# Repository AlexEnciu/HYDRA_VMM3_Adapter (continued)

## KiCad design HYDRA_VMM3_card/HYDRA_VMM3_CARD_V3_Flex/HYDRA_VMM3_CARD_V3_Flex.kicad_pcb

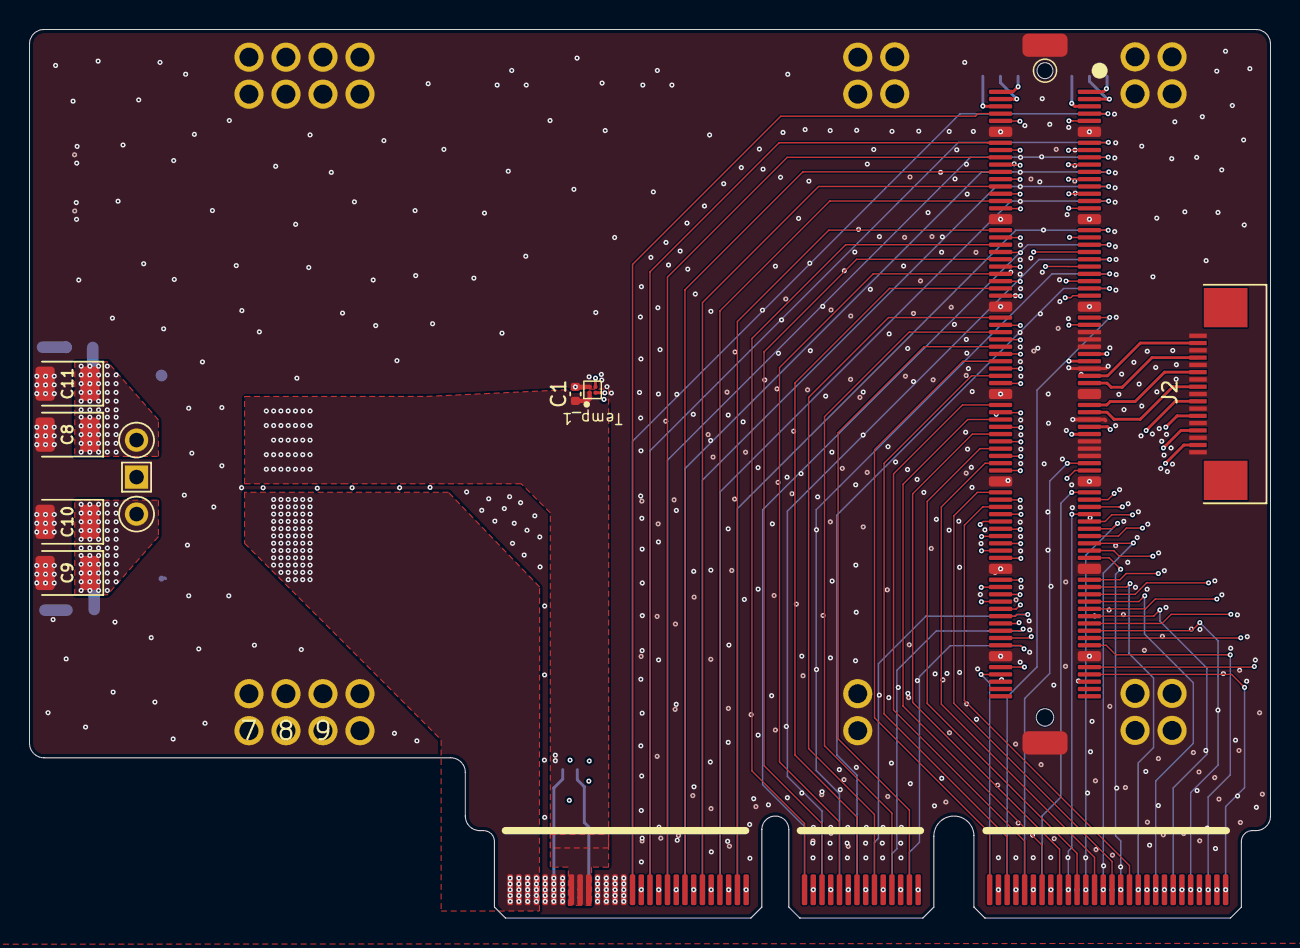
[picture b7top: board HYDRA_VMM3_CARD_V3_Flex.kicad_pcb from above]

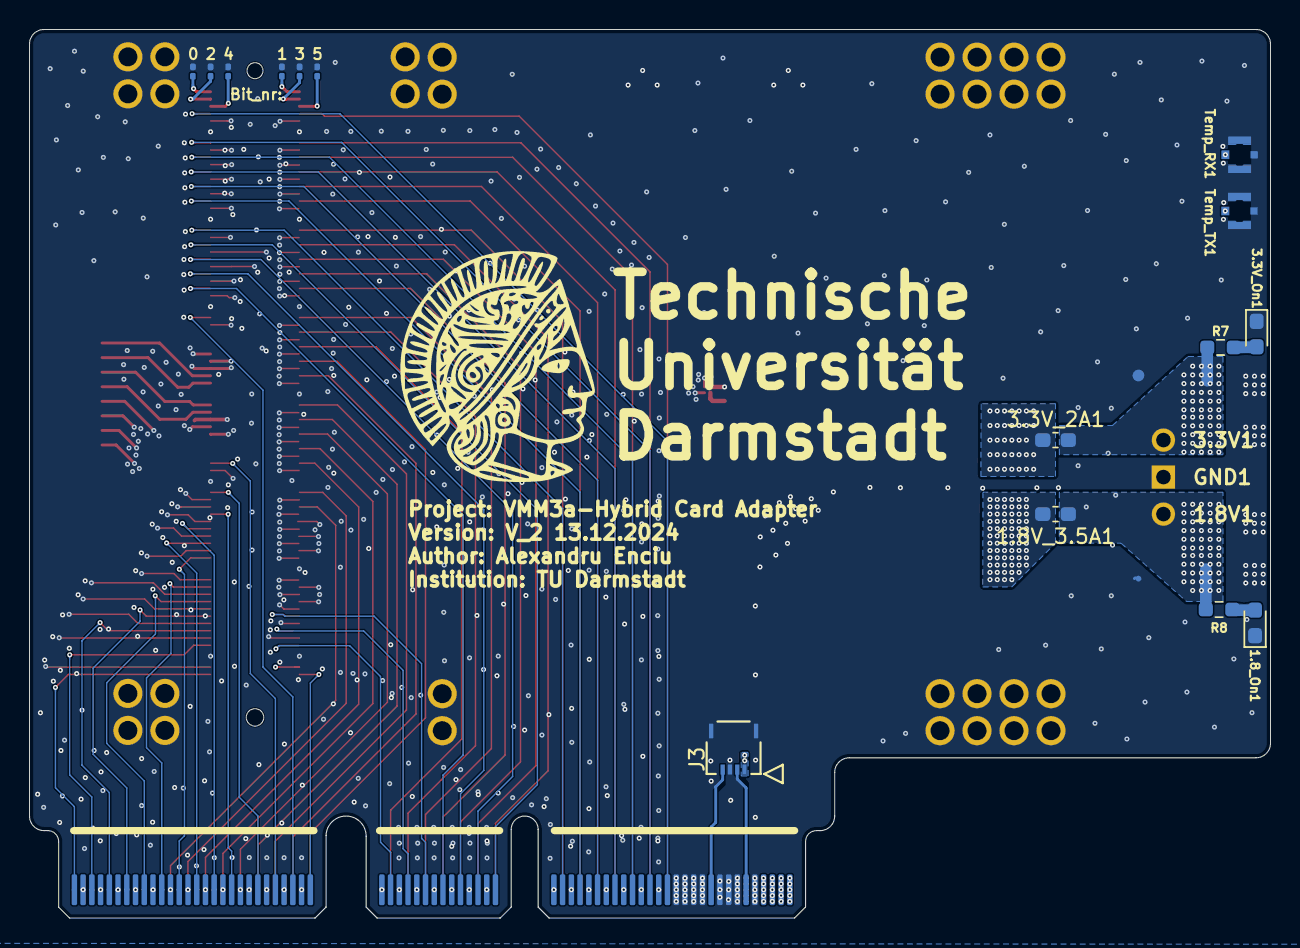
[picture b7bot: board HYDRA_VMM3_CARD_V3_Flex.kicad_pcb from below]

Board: 8 copper layers, 85.2 x 61.0 mm, 43 parts (15 on the bottom side), 137 nets.

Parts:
1, 2, 4, 5, 7, 8, 9, 11, 12, 13, 14, 15, 17, 20, 23, 24: (no value)
1.8V1: 1.8V; TestPoint_Pad_D2.5mm
1.8V_3.5A1: 2.5A; Fuse_0603_1608Metric_Pad1.05x0.95mm_HandSolder
1.8_On1, 3.3V_On1: LED; LED_0603_1608Metric_Pad1.05x0.95mm_HandSolder
3.3V1: 3.3V; TestPoint_Pad_D2.5mm
3.3V_2A1: 2A; Fuse_0603_1608Metric_Pad1.05x0.95mm_HandSolder
C1: 100nF; C_0402_1005Metric
C8, C9, C10, C11: TCJB475M025R0100; CP_EIA-3528-12_Kemet-T
GND1: GND; TestPoint_Pad_2.5x2.5mm
J1: ME1014010101011; Edge-Card-Connector
J2: FPC: 68711714522; 68711714522
J3: FPC_4pin; CON_5034800440_MOL
R1, R2, R3, R4, R5, R6: 10k; R_0201_0603Metric
R7, R8: 1k; R_0603_1608Metric_Pad0.98x0.95mm_HandSolder
Temp_1: TMP104
Temp_RX1: 20449-001E-03; IPEX_20449-001E-03
Temp_TX1: 20449-001E-03; IPEX_20449-001E-03
U1: Hirose-FX10

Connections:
Ch_0: J1.A15, U1.7
Ch_1: J1.B15, U1.8
Ch_2: J1.A16, U1.9
Ch_3: J1.B16, U1.10
Ch_4: J1.A17, U1.11
Ch_5: J1.B17, U1.12
Ch_6: J1.A18, U1.13
Ch_7: J1.B18, U1.14
Ch_8: J1.A19, U1.15
Ch_9: J1.B19, U1.16
Ch_10: J1.A20, U1.17
Ch_11: J1.B20, U1.18
Ch_12: J1.A21, U1.19
Ch_13: J1.B21, U1.20
Ch_14: J1.A22, U1.21
Ch_15: J1.B22, U1.22
Ch_16: J1.A23, U1.23
Ch_17: J1.B23, U1.24
Ch_18: J1.A24, U1.25
Ch_19: J1.B24, U1.26
Ch_20: J1.A25, U1.27
Ch_21: J1.B25, U1.28
Ch_22: J1.A26, U1.29
Ch_23: J1.B26, U1.30
Ch_24: J1.A27, U1.31
Ch_25: J1.B27, U1.32
Ch_26: J1.A28, U1.33
Ch_27: J1.B28, U1.34
Ch_28: J1.A29, U1.35
Ch_29: J1.B29, U1.36
Ch_30: J1.A30, U1.37
Ch_31: J1.B30, U1.38
Ch_32: J1.A31, U1.39
Ch_33: J1.B31, U1.40
Ch_34: J1.A32, U1.41
Ch_35: J1.B32, U1.42
Ch_36: J1.A33, U1.43
Ch_37: J1.B33, U1.44
Ch_38: J1.A34, U1.45
Ch_39: J1.B34, U1.46
Ch_40: J1.A35, U1.47
Ch_41: J1.B35, U1.48
Ch_42: J1.A44, U1.49
Ch_43: J1.B36, U1.50
Ch_44: J1.A45, U1.51
Ch_45: J1.B37, U1.52
Ch_46: J1.A46, U1.53
Ch_47: J1.B38, U1.54
Ch_49: J1.B39, U1.56
Ch_51: J1.B40, U1.58
Ch_53: J1.B41, U1.60
Ch_54: J2.6, U1.61
Ch_55: J1.B42, U1.62
Ch_56: J2.8, U1.63
Ch_57: J1.B43, U1.64
Ch_59: J1.B44, U1.66
Ch_60: J2.16, U1.67
Ch_61: J1.B45, U1.68
Ch_62: J2.14, U1.69
Ch_63: J1.B46, U1.70
Ch_64: J2.12, U1.71
Ch_65: J1.B47, U1.72
Ch_66: J2.10, U1.73
Ch_67: J1.B48, U1.74
Ch_69: J1.B49, U1.76
Ch_70: J2.4, U1.77
Ch_71: J1.B50, U1.78
Ch_72: J2.2, U1.79
Ch_73: J1.B51, U1.80
Ch_75: J1.B52, U1.82
Ch_77: J1.B53, U1.84
Ch_79: J1.B54, U1.86
Ch_80: J1.A47, U1.87
Ch_81: J1.B55, U1.88
Ch_82: J1.A48, U1.89
Ch_83: J1.B56, U1.90
Ch_84: J1.A49, U1.91
Ch_85: J1.B57, U1.92
Ch_86: J1.A50, U1.93
Ch_87: J1.B58, U1.94
Ch_88: J1.A51, U1.95
Ch_89: J1.B59, U1.96
Ch_90: J1.A52, U1.97
Ch_91: J1.B60, U1.98
Ch_92: J1.A53, U1.99
Ch_93: J1.B61, U1.100
Ch_94: J1.A54, U1.101
Ch_95: J1.B70, U1.102
Ch_96: J1.A55, U1.103
Ch_97: J1.B65, U1.104
Ch_98: J1.A56, U1.105
Ch_99: J1.B69, U1.106
Ch_100: J1.A57, U1.107
Ch_101: J1.B64, U1.108
Ch_102: J1.A58, U1.109
Ch_103: J1.B68, U1.110
Ch_104: J1.A59, U1.111
Ch_105: J1.B67, U1.112
Ch_106: J1.A60, U1.113
Ch_107: J1.B63, U1.114
Ch_108: J1.A61, U1.115
Ch_109: J1.B66, U1.116
Ch_110: J1.A62, U1.117
Ch_111: J1.B62, U1.118
Ch_112: J1.A63, U1.119
Ch_113: J1.A36, U1.120
Ch_114: J1.A64, U1.121
Ch_115: J1.A37, U1.122
Ch_116: J1.A65, U1.123
Ch_117: J1.A38, U1.124
Ch_118: J1.A66, U1.125
Ch_119: J1.A39, U1.126
Ch_120: J1.A67, U1.127
Ch_121: J1.A40, U1.128
Ch_122: J1.A68, U1.129
Ch_123: J1.A41, U1.130
Ch_124: J1.A69, U1.131
Ch_125: J1.A42, U1.132
Ch_126: J1.A70, U1.133
Ch_127: J1.A43, U1.134
GND: 1.1, 1.8_On1.1 (K), 2.1, 3.3V_On1.1 (K), 4.1, 5.1, 7.1, 8.1, 9.1, 11.1, 12.1, 13.1, 14.1, 15.1, 17.1, 20.1, 23.1, 24.1, C1.2, C8.2, C9.2, C10.2, C11.2, GND1.1, J1.A5, J1.A7, J1.A8, J1.A9, J1.A11, J1.A12, J1.A13, J1.A14, J1.B5, J1.B6, J1.B7, J1.B11, J1.B12, J1.B13, J1.B14, J2.1, J2.3, J2.5, J2.7, J2.9, J2.11, J2.13, J2.15, J2.17, J3.3, J3.P1 (Pin_5), J3.P2 (Pin_6), R1.2, R2.2, R3.2, R4.2, R5.2, R6.2, Temp_1.2 (GND), Temp_RX1.2, Temp_RX1.3, Temp_RX1.4, Temp_TX1.2, Temp_TX1.3, Temp_TX1.4, U1.55, U1.57, U1.59, U1.65, U1.75, U1.81, U1.83, U1.85, U1.141 (GND)
Heimtime: J1.A10, J3.4
Master_Trigg: J1.A6, J3.2
unnamed: 1.8_On1.2 (A), R8.2
unnamed: 3.3V_On1.2 (A), R7.2
P1: 3.3V_2A1.1, C1.1, J1.B8, J1.B9, J1.B10, J3.1, Temp_1.1 (V+)
P1_Out: 3.3V1.1, 3.3V_2A1.2, C8.1, C11.1, R7.1
P2: 1.8V_3.5A1.1, J1.A1, J1.A2, J1.A3, J1.A4, J1.B1, J1.B2, J1.B3, J1.B4
P2_Out: 1.8V1.1, 1.8V_3.5A1.2, C9.1, C10.1, R8.1
RX: Temp_1.4 (RX), Temp_RX1.1
TX: Temp_1.3 (TX), Temp_TX1.1
bit_0: R1.1, U1.1
bit_1: R2.1, U1.2
bit_2: R3.1, U1.3
bit_3: R4.1, U1.4
bit_4: R5.1, U1.5
bit_5: R6.1, U1.6

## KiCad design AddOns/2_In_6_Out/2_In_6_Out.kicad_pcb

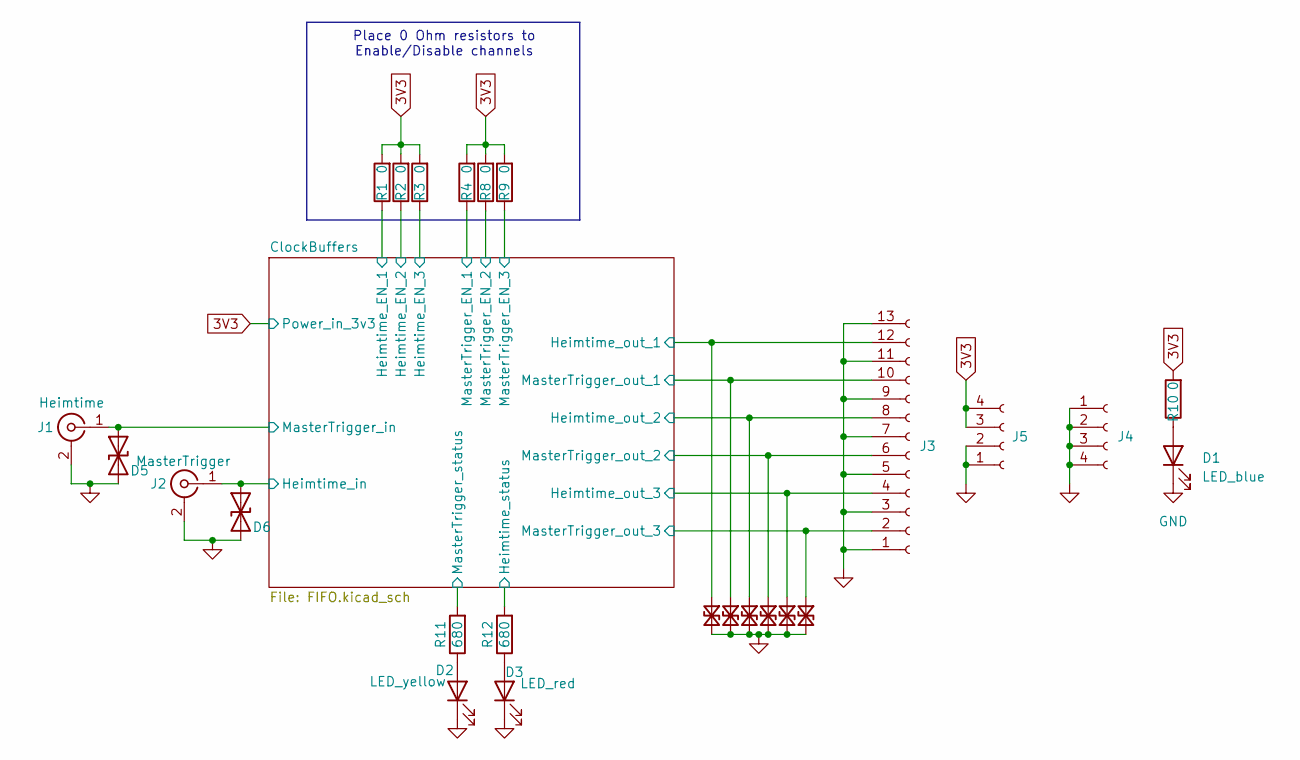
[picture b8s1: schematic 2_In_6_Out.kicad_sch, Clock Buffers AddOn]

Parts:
D1: LED_blue; LED_0603_1608Metric
D2: LED_yellow; LED_0603_1608Metric
D3: LED_red; LED_0603_1608Metric
D5, D6, D7, D8, D9, D10, D11, D13: SP1333-01UTG; D_0201_0603Metric
J1: Heimtime; SAMTEC_MCX-J-P-X-RA-SM1
J2: MasterTrigger; SAMTEC_MCX-J-P-X-RA-SM1
J3: Conn_01x13_Socket; PinHeader_1x13_P1.27mm_Vertical
J4, J5: Conn_01x04_Socket; PinHeader_1x04_P1.27mm_Vertical
R1, R2, R3, R4, R8, R9: 0; R_0402_1005Metric
R10: 0; R_0603_1608Metric
R11, R12: 680; R_0402_1005Metric

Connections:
3V3: J5.3, J5.4, R1.2, R2.2, R3.2, R4.2, R8.2, R9.2, R10.2; also elsewhere on the board
/ClockBuffers/Heimtime_EN_1: R1.1; also elsewhere on the board
/ClockBuffers/Heimtime_EN_2: R2.1; also elsewhere on the board
/ClockBuffers/Heimtime_EN_3: R3.1; also elsewhere on the board
/ClockBuffers/Heimtime_in: D6.1 (A1), J2.1 (In); also elsewhere on the board
/ClockBuffers/Heimtime_out_1: D13.1 (A1), J3.12; also elsewhere on the board
/ClockBuffers/Heimtime_out_2: D8.1 (A1), J3.8; also elsewhere on the board
/ClockBuffers/Heimtime_out_3: D10.1 (A1), J3.4; also elsewhere on the board
/ClockBuffers/Heimtime_status: R12.2; also elsewhere on the board
/ClockBuffers/MasterTrigger_EN_1: R4.1; also elsewhere on the board
/ClockBuffers/MasterTrigger_EN_2: R8.1; also elsewhere on the board
/ClockBuffers/MasterTrigger_EN_3: R9.1; also elsewhere on the board
/ClockBuffers/MasterTrigger_in: D5.1 (A1), J1.1 (In); also elsewhere on the board
/ClockBuffers/MasterTrigger_out_1: D7.1 (A1), J3.10; also elsewhere on the board
/ClockBuffers/MasterTrigger_out_2: D9.1 (A1), J3.6; also elsewhere on the board
/ClockBuffers/MasterTrigger_out_3: D11.1 (A1), J3.2; also elsewhere on the board
/ClockBuffers/MasterTrigger_status: R11.2; also elsewhere on the board
GND: D1.1 (K), D2.1 (K), D3.1 (K), D5.2 (A2), D6.2 (A2), D7.2 (A2), D8.2 (A2), D9.2 (A2), D10.2 (A2), D11.2 (A2), D13.2 (A2), J1.2 (Ext), J2.2 (Ext), J3.1, J3.3, J3.5, J3.7, J3.9, J3.11, J3.13, J4.1, J4.2, J4.3, J4.4, J5.1, J5.2; also elsewhere on the board
unnamed: D1.2 (A), R10.1
unnamed: D2.2 (A), R11.1
unnamed: D3.2 (A), R12.1

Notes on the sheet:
Place 0 Ohm resistors to Enable/Disable channels

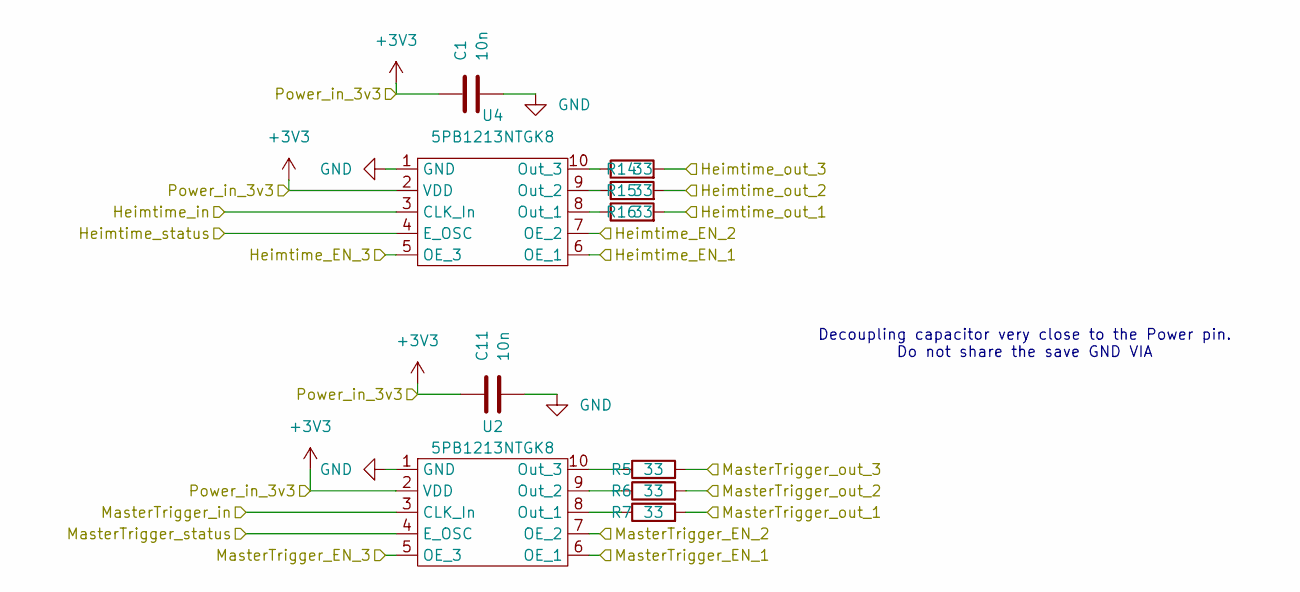
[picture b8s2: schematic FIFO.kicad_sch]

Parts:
C1, C11: 10n; C_0402_1005Metric
R5, R6, R7, R14, R15, R16: 33; R_0402_1005Metric
U2, U4: 5PB1213NTGK8

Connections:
3V3: C1.1, C11.1, U2.2 (VDD), U4.2 (VDD); also elsewhere on the board
/ClockBuffers/Heimtime_EN_1: U4.6 (OE_1); also elsewhere on the board
/ClockBuffers/Heimtime_EN_2: U4.7 (OE_2); also elsewhere on the board
/ClockBuffers/Heimtime_EN_3: U4.5 (OE_3); also elsewhere on the board
/ClockBuffers/Heimtime_in: U4.3 (CLK_In); also elsewhere on the board
/ClockBuffers/Heimtime_out_1: R16.2; also elsewhere on the board
/ClockBuffers/Heimtime_out_2: R15.2; also elsewhere on the board
/ClockBuffers/Heimtime_out_3: R14.2; also elsewhere on the board
/ClockBuffers/Heimtime_status: U4.4 (E_OSC); also elsewhere on the board
/ClockBuffers/MasterTrigger_EN_1: U2.6 (OE_1); also elsewhere on the board
/ClockBuffers/MasterTrigger_EN_2: U2.7 (OE_2); also elsewhere on the board
/ClockBuffers/MasterTrigger_EN_3: U2.5 (OE_3); also elsewhere on the board
/ClockBuffers/MasterTrigger_in: U2.3 (CLK_In); also elsewhere on the board
/ClockBuffers/MasterTrigger_out_1: R7.2; also elsewhere on the board
/ClockBuffers/MasterTrigger_out_2: R6.2; also elsewhere on the board
/ClockBuffers/MasterTrigger_out_3: R5.2; also elsewhere on the board
/ClockBuffers/MasterTrigger_status: U2.4 (E_OSC); also elsewhere on the board
GND: C1.2, C11.2, U2.1 (GND), U4.1 (GND); also elsewhere on the board
unnamed: R7.1, U2.8 (Out_1)
unnamed: R6.1, U2.9 (Out_2)
unnamed: R5.1, U2.10 (Out_3)
unnamed: R16.1, U4.8 (Out_1)
unnamed: R15.1, U4.9 (Out_2)
unnamed: R14.1, U4.10 (Out_3)

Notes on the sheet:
Decoupling capacitor very close to the Power pin. Do not share the save GND VIA

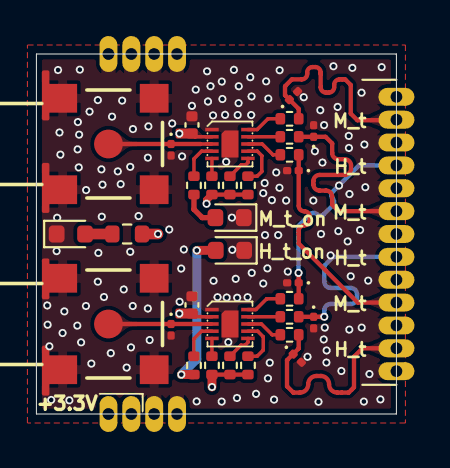
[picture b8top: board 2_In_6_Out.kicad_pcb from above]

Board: 4 copper layers, 20.0 x 20.0 mm, 35 parts (0 on the bottom side), 27 nets.

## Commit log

2025-07-14 Adjust C7 footprint position on PSU Stamp PCB
    Moved the C7 capacitor footprint to new coordinates (138.38, 74.27) on the Spartan7_PSU_Stamp_V0.kicad_pcb file for improved layout. Updated backup ZIP to reflect latest PCB changes.
2025-07-15 Add USB-C power and TPS7A2033PDBVR symbol
    Added USB_C_Power schematic, new TPS7A2033PDBVR symbol and library, and updated net names and layout for improved clarity. Also included new backup files and made minor footprint and netlist adjustme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
2025-07-15 Update net assignments and add vias in KiCad PCB
    Reassigned several net numbers and names in Spartan7_PSU_Stamp_V0.kicad_pcb for improved clarity and consistency. Added multiple via definitions and updated related PCB segments. Removed old backup f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
2025-07-16 Add status LEDs and update power nets
    Added new 0402 LEDs (D1, D4) and supporting resistor (R12) for power-good status indication. Updated net assignments and replaced a capacitor footprint with an LED. Modified schematic and PCB files t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
2025-07-16 Update PCB netlist and add GND test point
    Renumbered and cleaned up net assignments in the KiCad PCB file, updated several resistor values, and added a new GND test point (J4). Also updated backup and plot files to reflect the latest schemat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
2025-07-16 Add pin header footprints and update PCB layout
    Replaced C14 footprint with a pin header (J10), added new pin headers J11 and J25, and updated the PCB layout parameters. Also swapped C13 and C14 positions and made related changes to the BOM and ba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
2025-08-01 Add initial Spartan7 TriggerController PCB files
    Added KiCad project files, schematic, PCB layout, symbol and footprint libraries, backup archives, and supporting documentation for the Spartan7 TriggerController. This commit establishes the base ha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
2025-08-07 Update PCB layout and net assignments for new capacitors
    Added new nets and updated net assignments for several capacitors (C11, C12, C13, C14, C18, C19, C20, C21) in the PCB layout. Modified footprints, positions, and values for various components includi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
2025-08-07 Add stiffener models and update PCB stackup/materials
    Added STEP and SLDPRT models for 4-pin and 17-pin stiffeners and referenced them in the PCB layout. Updated stackup layers with material, epsilon_r, and loss_tangent properties. Removed obsolete tear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
2025-08-19 Update PCB layout and add new backup and SPICE files
    Added new backup ZIP files and SPICE simulation files for Clock_Buffers_1-16 and HYDRA_VMM3_CARD_V3_Flex, while removing outdated backup files. Updated multiple footprints and component placements in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
2026-02-08 Convert LED to SMD; adjust stackup & silk
    Update PCB layout: replace through-hole LED footprint with an LED_SMD 0603 footprint (pads converted to SMD roundrect, 3D model updated), adjust footprint positions/orientations and text/font sizes. 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
